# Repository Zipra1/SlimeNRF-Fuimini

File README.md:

# SlimeNRF-Fuimini-PCB

Supermini-based PCB for nRF flavoured SlimeVR body trackers.

Schematic based off [SlimeVR-Tracker-nRF-PCB](https://github.com/SlimeVR/SlimeVR-Tracker-nRF-PCB)

Cat drawing on the PCB by [my amazing beatuifiul wife](https://www.tumblr.com/circlegirl?source=share)

Detailed README.md files are in folders.

## i sell these!
You can buy them [at my website.](https://macroplastics.ca/)
Rather contact me directly? You can find me here https://discord.gg/vpxSHmUSXH or email me at fui@macroplastics.ca
Curious where prices come from? View the entire spreadsheet [here.](https://docs.google.com/spreadsheets/d/1XSO24xmqJCDWiKMqtOlyQpGnMuTRnx9r1LJr4mPH8TY/edit?usp=sharing)

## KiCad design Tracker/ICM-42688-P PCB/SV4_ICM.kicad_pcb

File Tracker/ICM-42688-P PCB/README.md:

# This is currently NON-FUNCTIONAL
It is in the midst of an update to SPI, as well as some extra features. Please check out Commit `f3380db` for the currently functional version.

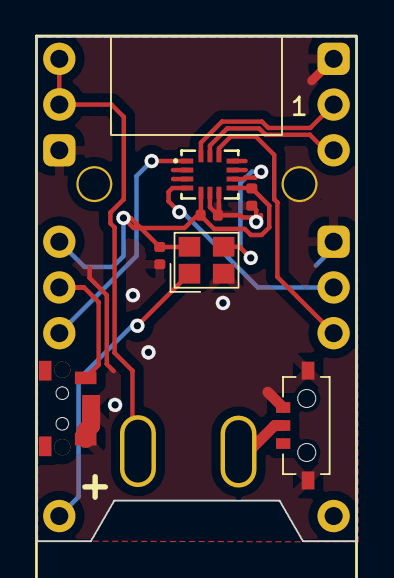
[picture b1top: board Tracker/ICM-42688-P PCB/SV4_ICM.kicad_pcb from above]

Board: 2 copper layers, 17.8 x 28.0 mm, 10 parts (0 on the bottom side), 12 nets.

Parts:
C3, C4, C8: 100nF; C_0402_1005Metric
S1: GT-TC020B-H035-L05
TP1, TP2: BCon; 2_4-1.5_3.5_1
U1: SuperMini nRF52840; SuperMini_nRF52840_AH_USBdn
U2: ICM-42688-P
U4: K3-1295S-E1
X1: OK252032.768KJBA4SL

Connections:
+3V3: C3.2, C4.2, C8.2, U1.16 (3V3), U2.5 (VDDIO), U2.8 (VDD), X1.4 (VDD)
CLK: U2.9 (INT2/FSYNC/CLKIN), X1.3 (OUT)
CS: U1.6 (P0.20), U2.12 (AP_CS)
GND: C3.1, C4.1, C8.1, S1.2, S1.3, U1.4 (GND), U1.14 (GND), U1.28 (GND), U2.6 (GND), U2.7 (RESV), U4.3, U4.4, U4.5, X1.2 (GND)
INT1: U1.5 (P0.17), U2.4 (INT1/INT)
unnamed: TP1.1, U1.13 (BAT+), U1.29 (BAT+)
unnamed: TP2.1, U4.2
unnamed: S1.1, U1.17 (P0.31-LF)
OSC_EN: U1.22 (P1.11-LF), X1.1 (EN)
SCL: U1.2 (P0.08), U2.13 (AP_SCL/AP_SCLK)
SDA: U1.1 (P0.06), U2.14 (AP_SDA/AP_SDIO/AP_SDI)
SDO: U1.18 (P0.29-LF), U2.1 (AP_SDO/AP_AD0)

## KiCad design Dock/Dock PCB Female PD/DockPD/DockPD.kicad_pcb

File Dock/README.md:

## Charging dock
Currently this repo only contains the files for a dock with 6 trackers. Due to technical limitations I can't provide a parametric file. I will add 5,6,7,8,9,& 10 docks later.\
If you want a dock with # of trackers that isn't included here, feel free to [contact me on discord](https://discord.gg/vpxSHmUSXH) for the files.\
Spots for rubber feet fit standard 6mm adhesive non-slip rubber feet.\
Wall mounts are for generic 1¼" drywall screws.\
Uses [Treedix USB Type-C Breakout Board](https://www.amazon.ca/gp/product/B096M2HQLK) as the USB C input. This isn't a custom PCB because only one is required per dock, it's cheaper to order these than a custom pcb in small quantities.\

\

* The .3mf is for Orca Slicer. I print with a Bambu Labs P1S.

 \
 \

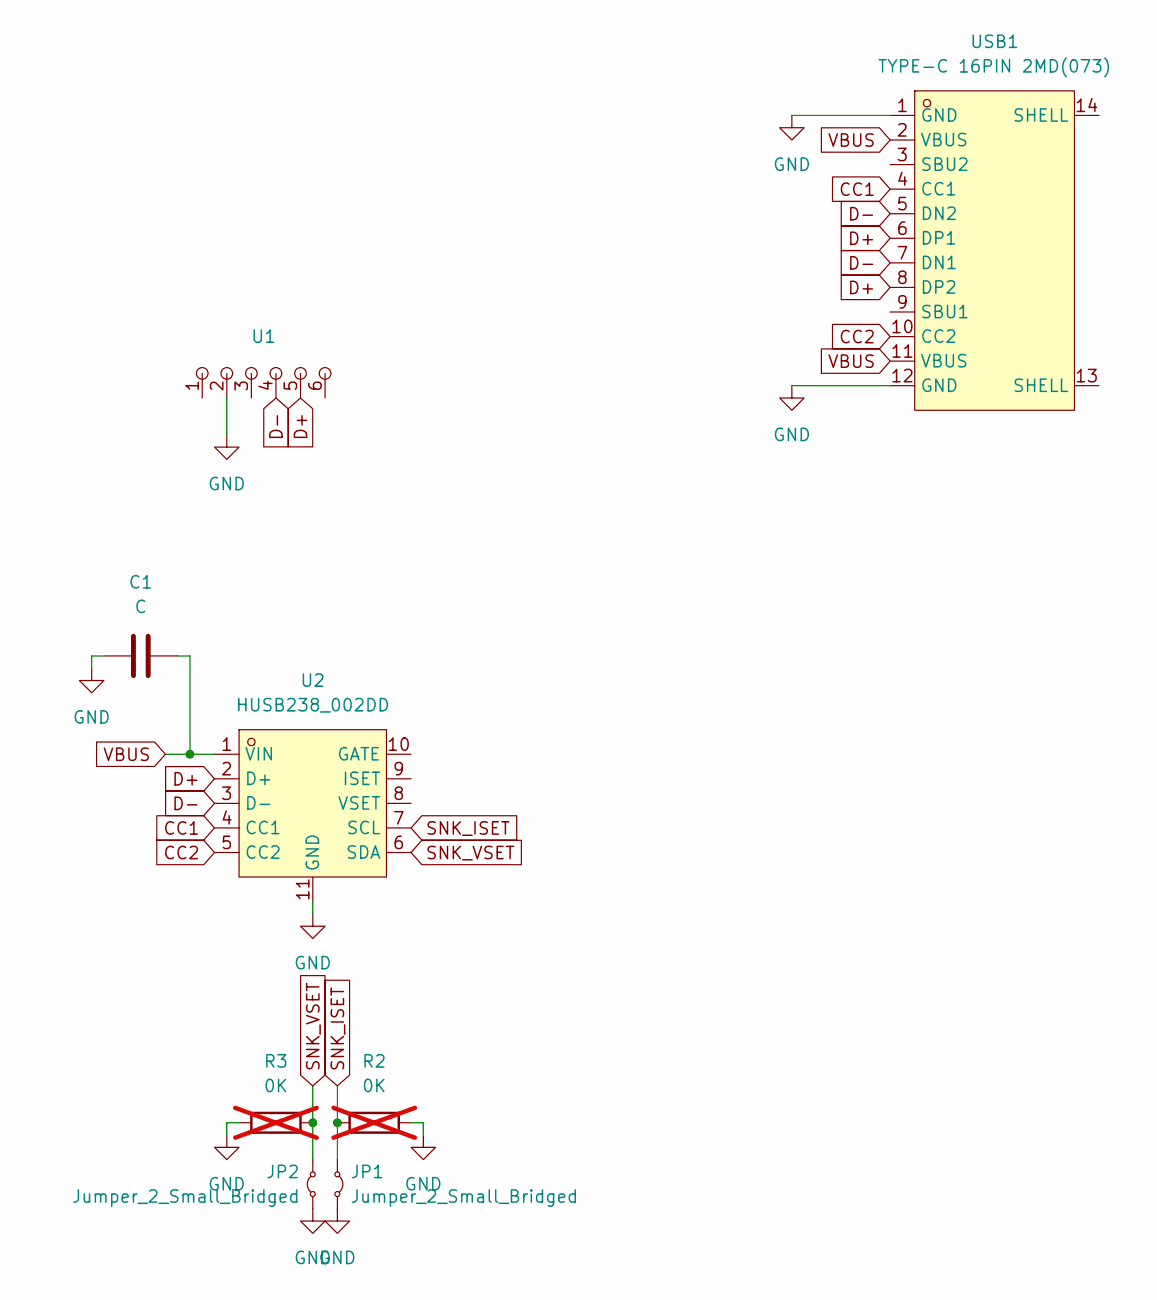
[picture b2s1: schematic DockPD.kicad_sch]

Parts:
C1: C; C_0402_JLC
JP1, JP2: Jumper_2_Small_Bridged; SolderJumper-2_P1.3mm_Open_TrianglePad1.0x1.5mm
R2, R3: 0K; R_Axial_DIN0204_L3.6mm_D1.6mm_P7.62mm_Horizontal; not fitted
U1: PinHeader_1x06_P2.54mm_Vertical
U2: HUSB238_002DD; DFN-10_L3.0-W3.0-P0.50-BL-EP2.5; LCSC Part C7471904
USB1: TYPE-C 16PIN 2MD(073); USB-C-SMD_TYPE-C-6PIN-2MD-073; LCSC Part C2765186

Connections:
CC1: U2.4 (CC1), USB1.4 (CC1)
CC2: U2.5 (CC2), USB1.10 (CC2)
D+: U1.5, U2.2 (D+), USB1.6 (DP1), USB1.8 (DP2)
D-: U1.4, U2.3 (D-), USB1.5 (DN2), USB1.7 (DN1)
GND: C1.1, JP1.2 (B), JP2.2 (B), R2.2, R3.1, U1.2, U2.11 (GND), USB1.1 (GND), USB1.12 (GND)
SNK_ISET: JP1.1 (A), R2.1, U2.7 (SCL)
SNK_VSET: JP2.1 (A), R3.2, U2.6 (SDA)
VBUS: C1.2, U2.1 (VIN), USB1.2 (VBUS), USB1.11 (VBUS)

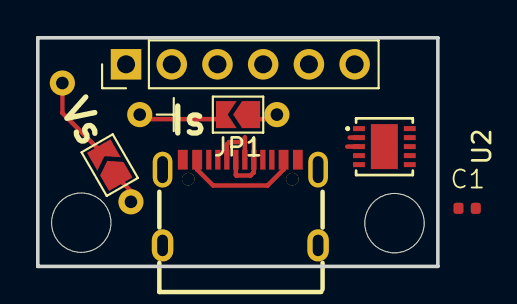
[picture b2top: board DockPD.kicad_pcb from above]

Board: 2 copper layers, 22.2 x 12.7 mm, 8 parts (0 on the bottom side), 8 nets.

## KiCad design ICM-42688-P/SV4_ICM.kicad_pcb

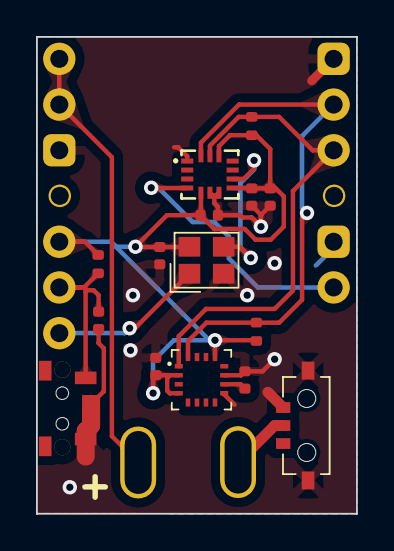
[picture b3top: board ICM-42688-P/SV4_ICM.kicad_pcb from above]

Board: 2 copper layers, 17.8 x 26.5 mm, 18 parts (0 on the bottom side), 11 nets.

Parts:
C1, C4, C8: 100nF; C_0402_1005Metric
C2: 1uF; C_0402_1005Metric
C3: 10nF; C_0402_1005Metric
C5: 10uF; C_0402_1005Metric
C7: 2.2uF; C_0402_1005Metric
R1, R2: 10k; R_0402_1005Metric
R5: 200k; R_0402_1005Metric
S1: GT-TC020B-H035-L05
TP1, TP2: BCon; 2_4-1.5_3.5_1
U1: SuperMini nRF52840; SuperMini_nRF52840_AH_USBdn
U2: ICM-42688-P
U3: MMC5983MA
U4: K3-1295S-E1
X1: OK252032.768KJBA4SL

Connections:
+3V3: C2.2, C3.2, C4.2, C7.2, C8.2, R1.2, R2.2, R5.2, U1.16 (3V3), U2.5 (VDDIO), U2.8 (VDD), U2.12 (AP_CS), U3.2 (VDD), U3.4 (SPI_CS), U3.13 (VDDIO), X1.4 (VDD)
GND: C1.1, C2.1, C3.1, C4.1, C5.1, C7.1, C8.1, S1.2, S1.3, U1.4 (GND), U1.14 (GND), U1.28 (GND), U2.1 (AP_SDO/AP_AD0), U2.6 (GND), U2.7 (RESV), U3.9 (GND), U3.11 (GND), U4.3, U4.4, U4.5, X1.2 (GND)
INT1: U1.5 (P0.17), U2.4 (INT1/INT)
unnamed: TP1.1, U1.13 (BAT+), U1.29 (BAT+)
unnamed: TP2.1, U4.2
unnamed: C1.2, R5.1, S1.1, U1.17 (P0.31-LF)
unnamed: U2.9 (INT2/FSYNC/CLKIN), X1.3 (OUT)
unnamed: C5.2, U3.10 (CAP)
OSC_EN: U1.18 (P0.29-LF), X1.1 (EN)
SCL: R1.1, U1.2 (P0.08), U2.13 (AP_SCL/AP_SCLK), U3.1 (SCL)
SDA: R2.1, U1.1 (P0.06), U2.14 (AP_SDA/AP_SDIO/AP_SDI), U3.16 (SDA)

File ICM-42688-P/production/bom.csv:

Designator,Footprint,Quantity,Value,LCSC Part #
"C1, C4, C8",0402,3,100nF,C14663
C2,0402,1,1uF,C14663
C3,0402,1,10nF,C14663
C5,0402,1,10uF,C14663
C7,0402,1,2.2uF,C14663
"R1, R2",0402,2,10k,C23162
R5,0402,1,200k,C23162
S1,GT-TC020B-H035-L05,1,GT-TC020B-H035-L05,
"TP1, TP2",2_4-1.5_3.5_1,2,BCon,
U2,ICM-42688-P,1,ICM-42688-P,
U3,MMC5983MA,1,MMC5983MA,
U4,K3-1295S-E1,1,K3-1295S-E1,
X1,OK252032.768KJBA4SL,1,~,

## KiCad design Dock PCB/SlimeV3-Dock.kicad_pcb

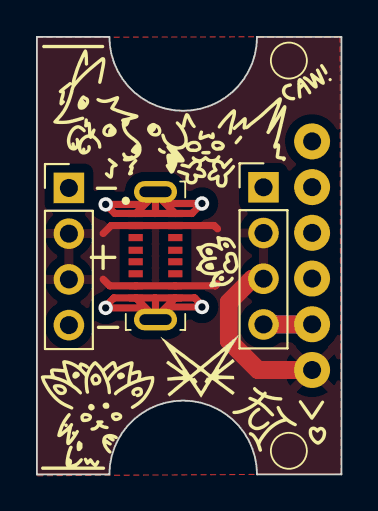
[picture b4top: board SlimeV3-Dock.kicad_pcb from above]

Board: 2 copper layers, 16.9 x 24.3 mm, 4 parts (0 on the bottom side), 2 nets.

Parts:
J1, J2: DNP; PinHeader_1x04_P2.54mm_Vertical
U1: DNP; Treedix USB Type-C
U2: YTC-TC16S-128

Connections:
GND: J1.1, J1.4, J2.1, J2.4, U1.2 (GND), U2.A1 (GND), U2.A12 (GND), U2.B1 (GND), U2.B12 (GND), U2.EH1 (EP), U2.EH2 (EP)
VBUS: J1.2, J1.3, J2.2, J2.3, U1.1 (VBUS), U2.A4 (VBUS), U2.A9 (VBUS), U2.B4 (VBUS), U2.B9 (VBUS)

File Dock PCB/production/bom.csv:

Designator,Footprint,Quantity,Value,LCSC Part #
"J1, J2",PinHeader_1x04_P2.54mm_Vertical,2,DNP,
U1,Treedix USB Type-C,1,DNP,
U2,YTC-TC16S-128,1,YTC-TC16S-128,

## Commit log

2024-11-03 Added all KiCad project files for board with ICM-42688-P + MMC5983MA
2024-11-03 .gitignore now includes production backup files
2024-11-03 Delete ICM-42688-P/production/backups directory
    Deleted production backups from git
2024-11-03 Added credit for cat art on PCB
2024-11-03 Added credit for cat art artist. Fixed .gitignore again
2024-11-03 i really said "added credit for pcb cat art" and then didnt. I did it this time for real.
2024-11-03 Added case stl and step file.
2024-11-03 Improved printability for end cap
2024-11-03 Flipped internals for better pin placement & printability
2024-11-03 Changed wife compliment. Added typo.
2024-11-04 Case modifications: Filleted capped end. Added flex part for button. Adjusted end cap tolerances.
2024-11-04 Added 3mf file for Orca Slicer. Improved bridged areas. Increased button travel space.
2024-11-04 Fixed 3mf file. Reduced bridge distance. Fixed battery tray tolerances.
2024-11-04 Added disassembly holes. Added USB C cutout. Thickened top layer by 0.12mm
2024-11-04 Thickened light diffuser walls
2024-11-04 Added receiver case files. Restructured 3d models
2024-11-04 Fixed 3d model folder deletion. Oops :3
2024-11-04 - Added PCB push hole for easier disassembly - Increased pin push hole for SIM tools - Added disassembly slide to release battery tray - Added i2c pullups... I can't believe I forgot those. I already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
2024-11-04 Added readme for tracker prints
2024-11-04 Fixed tracker readme
2024-11-05 - Added second PCB push hole to even pressure while disassembling - Tightened pin tolerances - Increased battery tray length to double as an assembly tool and board stabilizer - Added logo on tracker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
2024-11-05 - Flipped internals. Again - Pushed pins toward center to take advantage of battery shape
2024-11-05 - Flipped internals. Again - Pushed pins toward center to take advantage of battery shape - Fixed button deflector - Lowered USB C cutout by 0.1mm
2024-11-05 - Added .3mf missing from last commit.
2024-11-06 - Added light diffuser - Increased internal height by 0.12mm - Lowered USB C cutout by 0.1mm again - Decreased USB C cutout wall by 0.2mm, now 0.8mm thick
2024-11-06 - Added light diffuser - Increased internal height by 0.12mm - Lowered USB C cutout by 0.1mm again - Decreased USB C cutout wall by 0.2mm, now 0.8mm thick - Updated readme's
2024-11-07 - Added fillets on strap loops and back side top edge - Detached shaft from balls on the phallic-shaped symbol - Chamfered pin insert holes by 0.12mm for printability
2024-11-07 Updated .step file with changes from last
2024-11-07 - Changed PCB "mirror" to 1mm NPTH, LED will shine through hole rather than reflect to side.
2024-11-09 Added dock PCB files
2024-11-09 Added README.md for Dock PCB
2024-11-09 Added README.md to dock PCB. Modified main README.md
2024-11-14 Added pin jig. Did not modify PCB, only opened for reference.
2024-11-14 Increased pin cutting jig width and length
2024-11-17 Added supermini debug jig. Moved case button location to match PCB.
2024-12-03 - Added dimensions to dock pcb - some other stuff probably that i forgot to write down
2024-12-06 - Increased body length by 2.2mm to allow more space for antenna. Was having signal strength issues. - Added 3d models for dock
2024-12-06 - Changed my amazing beatuifiul wife link from twitter to tumblr.
2024-12-08 - Added battery disconnect switch on PCB - Fixed dock dimension issues - Removed stl files from dock folder. Just split the step file in your slicer. - Added 3mf file for dock models. Compatible with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
2024-12-09 - Fixed dock dimensions. Again
2024-12-11 - Fixed dock length issue - Added wall mount to dock - Added disassembly slots to dock
2024-12-11 - Added spot for anti-slip feet on dock
2024-12-11 - Improved dock print profile - Increased dock anti-slip feet insert depth - Increased dock repair slit width
2024-12-12 - Reorganized file structure
2024-12-12 Fixed dock readme
2024-12-12 Improved dock readme
2024-12-12 - Improved dock readme
2024-12-12 - Added picture of treedix USB C breakout board
2024-12-12 - Fixed dock readme picture position
2024-12-12 - Fix dock readme picture positions again
2024-12-14 - Added ceiling mount - Added cable hook
2024-12-16 - Added logo to receiver model - Added link to pricing spreadsheet to readme
2024-12-17 - Added extension cable hook - Reorganized receiver 3d files - Added calibration jig
2024-12-24 - Moved resistor to avoid conflict with USB C port - Added PDF of schematic for SlimeVR Marketplace listing
2024-12-27 - Added slot in case to reach the battery disconenct switch - Decreased tolerances for case end cap
2024-12-28 - Added cutout on bottom of case for debug pins - Added user manual
2024-12-28 Added pdf files for printing instruction booklets
2024-12-29 - added colouring page in user manual - added 7-tracker dock files - updated main readme - added readme for user manual folder
2024-12-31 - Added button functions page in user manual - Added 10-tracker dock STEP file
2025-01-06 - Added testing jig 3d model - Added folder for jigs - Removed debouncing capacitor from PCB, not needed.
2025-01-14 im ngl im really struggling with git rn sorry no commit message
2025-01-17 - Update license to Attribution-ShareAlike 4.0 International
2025-02-13 - Changed speed for top layers in 3mf file - Added more pages to manual - Added 11-tracker dock
2025-04-11 only god knows how git works
2025-04-11 Compressed top.png and iso2.png. Added thumbnail.png
2025-05-09 - Updated user manual - Added 5 and 8 docks - Added holyIOT dongle photos - Added Extension cable explanation.psd - Added light guide to user manual - Remade button guide in user manual - Switched us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
2025-05-23 - Added maintenance page to user manual
2025-05-24 - Added shoulder strap cam lock model
2025-05-25 - Added shoulder strap back triangle - Added quick disconnect for chest harness. Cause putting the harness on the dock would be rather cumbersome.
2025-08-03 - Edited user manual but i forgot what I put. why didnt i commit it when I did that? - Added more strap solutions
2025-08-21 - Started updating pcb for spi, didn't ifnish lol use the last commit - Added
2025-08-21 - Added alternative chesty mount for slimmer fit but more difficult assembly.
2025-08-21 - Added PCB readme w/ warning
2025-11-10 - Updated calibration jig model
